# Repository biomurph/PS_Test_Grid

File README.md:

# PS_Test_Grid
Test grid for PS Hardware Revision

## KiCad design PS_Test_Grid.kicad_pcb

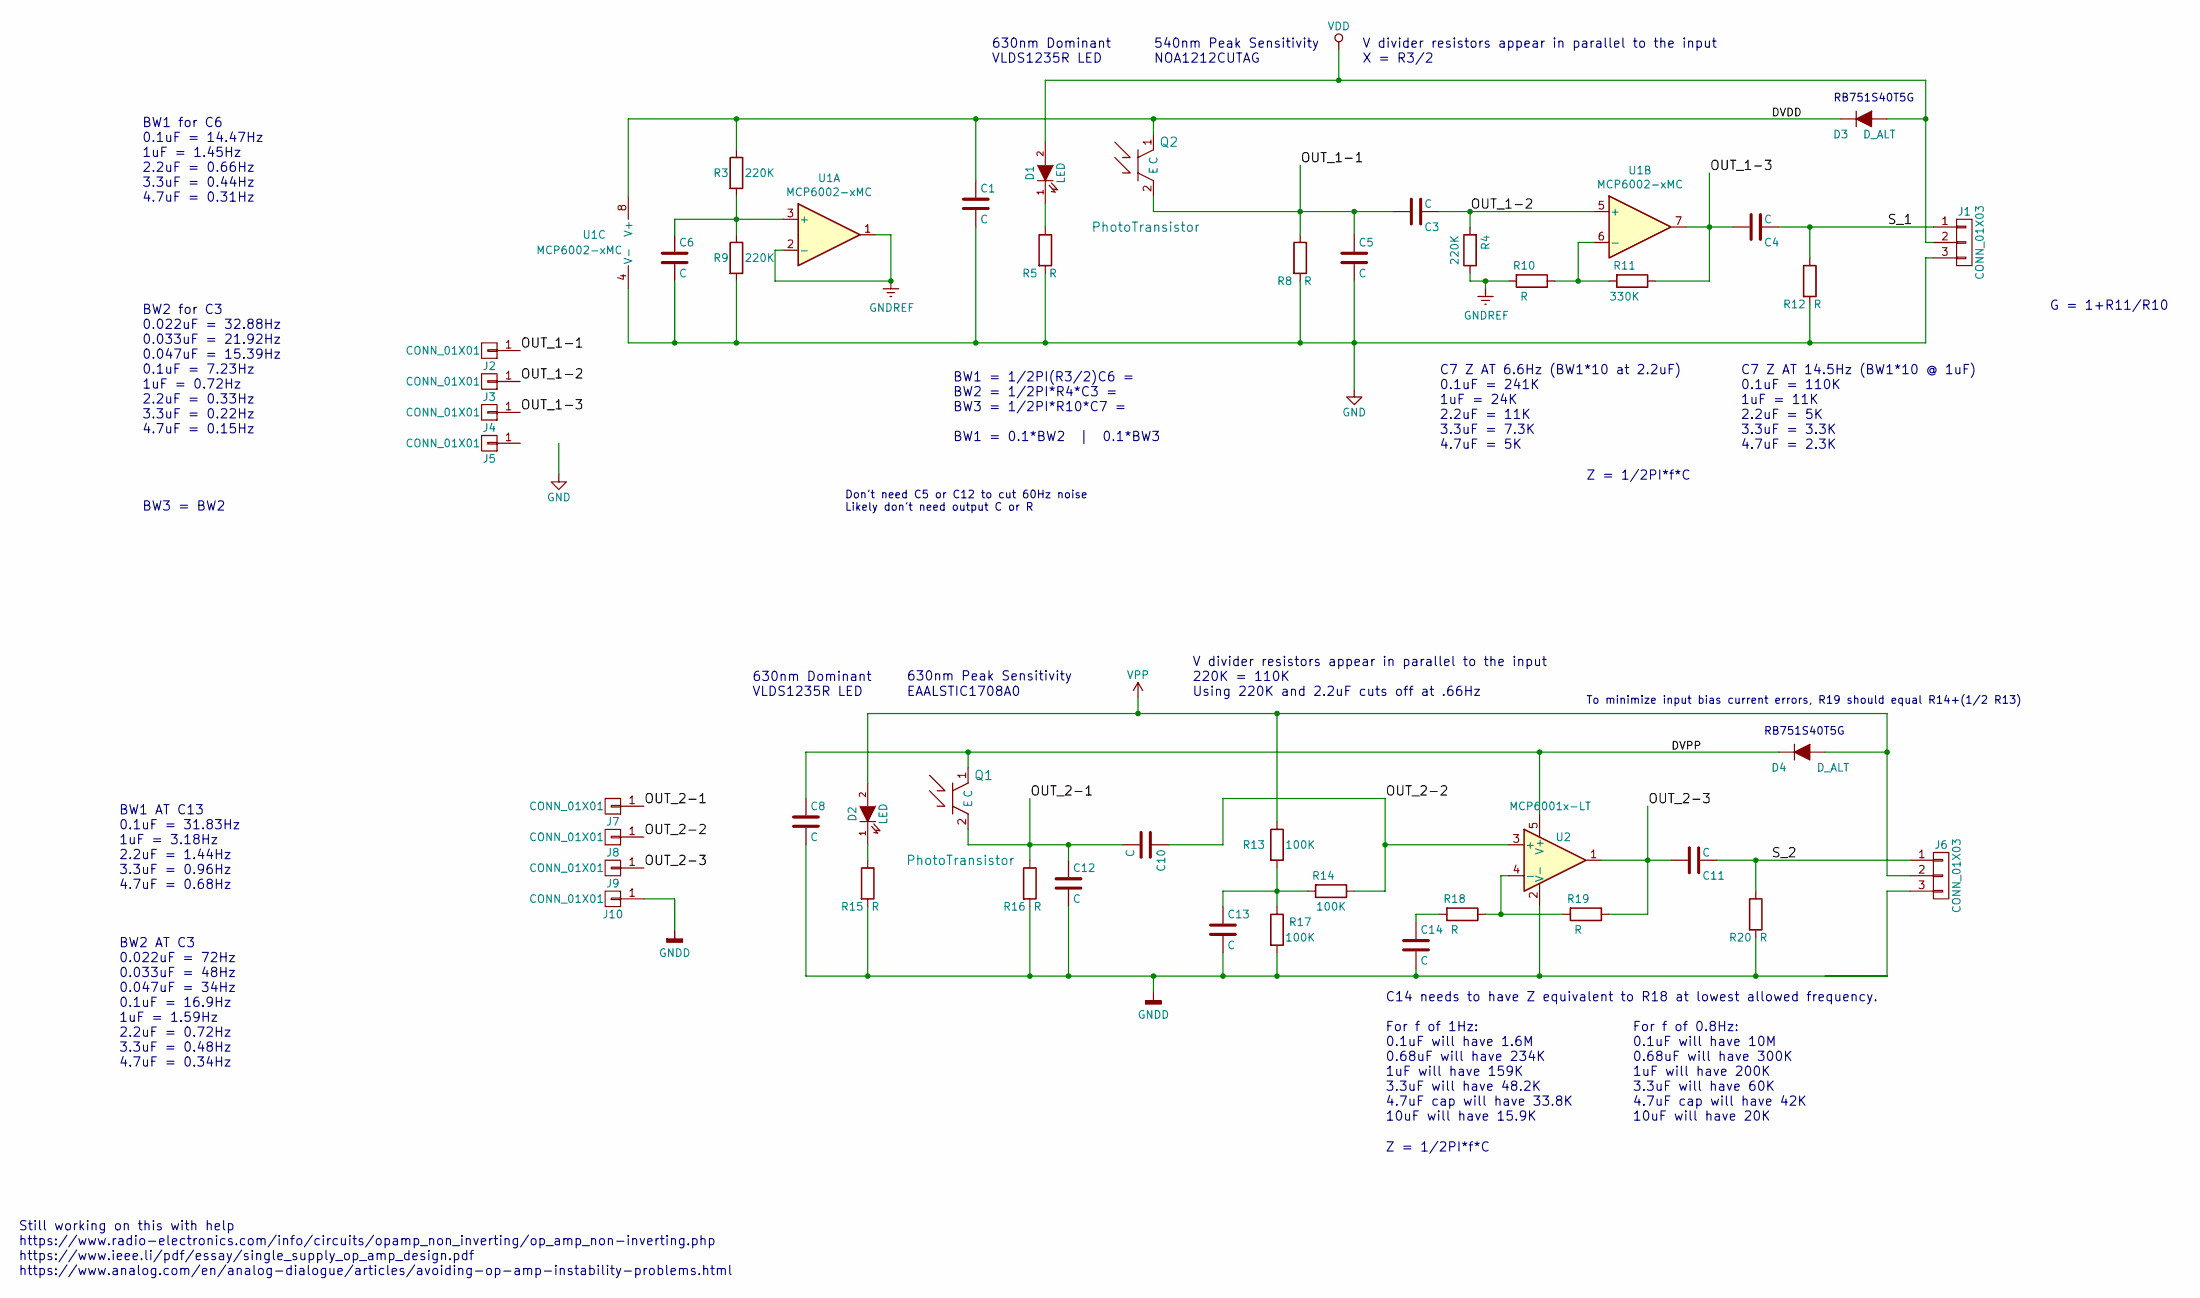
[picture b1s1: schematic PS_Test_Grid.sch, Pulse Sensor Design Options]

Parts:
C1, C3, C4, C5, C6, C8, C10, C11, C12, C13, C14: C; C_0603
D1, D2: LED; VLD1235R_LED
D3, D4: D_ALT; RB751S40T5G_DIODE
J1, J6: CONN_01X03; Pin_Header_Straight_1x03_Pitch2.54mm
J2, J3, J4, J5, J7, J8, J9, J10: CONN_01X01; Pin_Header_Straight_1x01_Pitch1.00mm
Q1, Q2: PhotoTransistor; EAALSTIC1708A0
R3, R4, R9: 220K; C_0603
R5, R8, R10, R12, R15, R16, R18, R19, R20: R; C_0603
R11: 330K; C_0603
R13, R14, R17: 100K; C_0603
U1: MCP6002-xMC; DFN-8-1EP_3x2mm_P0.5mm_EP1.75x1.45mm
U2: MCP6001x-LT; SOT-353_SC-70-5

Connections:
/DVDD: C1.1, D3.1 (K), Q2.1 (C), R3.1, U1.8 (V+)
/DVPP: C8.1, D4.1 (K), Q1.1 (C), U2.5 (V+)
/OUT_1-1: C3.2, C5.1, J2.1, Q2.2 (E), R8.1
/OUT_1-2: C3.1, J3.1, R4.2, U1.5 (+)
/OUT_1-3: C4.2, J4.1, R11.1, U1.7
/OUT_2-1: C10.2, C12.1, J7.1, Q1.2 (E), R16.1
/OUT_2-2: C10.1, J8.1, R14.1, U2.3 (+)
/OUT_2-3: C11.2, J9.1, R19.1, U2.1
/S_1: C4.1, J1.1, R12.1
/S_2: C11.1, J6.1, R20.1
GND: C1.2, C5.2, C6.2, J1.3, J5.1, R5.2, R8.2, R9.2, R12.2, U1.4 (V-), U1.9 (V-)
GNDD: C8.2, C12.2, C13.2, C14.2, J6.3, J10.1, R15.2, R16.2, R17.2, R20.2, U2.2 (V-)
GNDREF: R4.1, R10.2, U1.1, U1.2 (-)
unnamed: C6.1, R3.2, R9.1, U1.3 (+)
unnamed: C13.1, R13.2, R14.2, R17.1
unnamed: C14.1, R18.2
unnamed: D1.1 (K), R5.1
unnamed: D2.1 (K), R15.1
unnamed: R10.1, R11.2, U1.6 (-)
unnamed: R18.1, R19.2, U2.4 (-)
VDD: D1.2 (A), D3.2 (A), J1.2
VPP: D2.2 (A), D4.2 (A), J6.2, R13.1

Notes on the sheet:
EAALSTIC1708A0
V divider resistors appear in parallel to the input X = R3/2
Still working on this with help https://www.radio-electronics.com/info/circuits/opamp_non_inverting/op_amp_non-inverting.php https://www.ieee.li/pdf/essay/single_supply_op_amp_design.pdf https://www.analog.com/en/analog-dialogue/articles/avoiding-op-amp-instability-problems.html
V divider resistors appear in parallel to the input 220K = 110K Using 220K and 2.2uF cuts off at .66Hz
C14 needs to have Z equivalent to R18 at lowest allowed frequency. For f of 1Hz: 0.1uF will have 1.6M 0.68uF will have 234K 1uF will have 159K 3.3uF will have 48.2K 4.7uF cap will have 33.8K 10uF will have 15.9K
630nm Peak Sensitivity
630nm Dominant VLDS1235R LED
540nm Peak Sensitivity NOA1212CUTAG
For f of 0.8Hz: 0.1uF will have 10M 0.68uF will have 300K 1uF will have 200K 3.3uF will have 60K 4.7uF cap will have 42K 10uF will have 20K
Z = 1/2PI*f*C
BW1 = 1/2PI(R3/2)C6 = BW2 = 1/2PI*R4*C3 = BW3 = 1/2PI*R10*C7 = BW1 = 0.1*BW2 | 0.1*BW3
BW1 for C6 0.1uF = 14.47Hz 1uF = 1.45Hz 2.2uF = 0.66Hz 3.3uF = 0.44Hz 4.7uF = 0.31Hz
BW1 AT C13 0.1uF = 31.83Hz 1uF = 3.18Hz 2.2uF = 1.44Hz 3.3uF = 0.96Hz 4.7uF = 0.68Hz
BW2 for C3 0.022uF = 32.88Hz 0.033uF = 21.92Hz 0.047uF = 15.39Hz 0.1uF = 7.23Hz 1uF = 0.72Hz 2.2uF = 0.33Hz 3.3uF = 0.22Hz 4.7uF = 0.15Hz
BW3 = BW2
C7 Z AT 6.6Hz (BW1*10 at 2.2uF) 0.1uF = 241K 1uF = 24K 2.2uF = 11K 3.3uF = 7.3K 4.7uF = 5K
BW2 AT C3 0.022uF = 72Hz 0.033uF = 48Hz 0.047uF = 34Hz 0.1uF = 16.9Hz 1uF = 1.59Hz 2.2uF = 0.72Hz 3.3uF = 0.48Hz 4.7uF = 0.34Hz
C7 Z AT 14.5Hz (BW1*10 @ 1uF) 0.1uF = 110K 1uF = 11K 2.2uF = 5K 3.3uF = 3.3K 4.7uF = 2.3K
G = 1+R11/R10
RB751S40T5G
To minimize input bias current errors, R19 should equal R14+(1/2 R13)
Don’t need C5 or C12 to cut 60Hz noise Likely don’t need output C or R

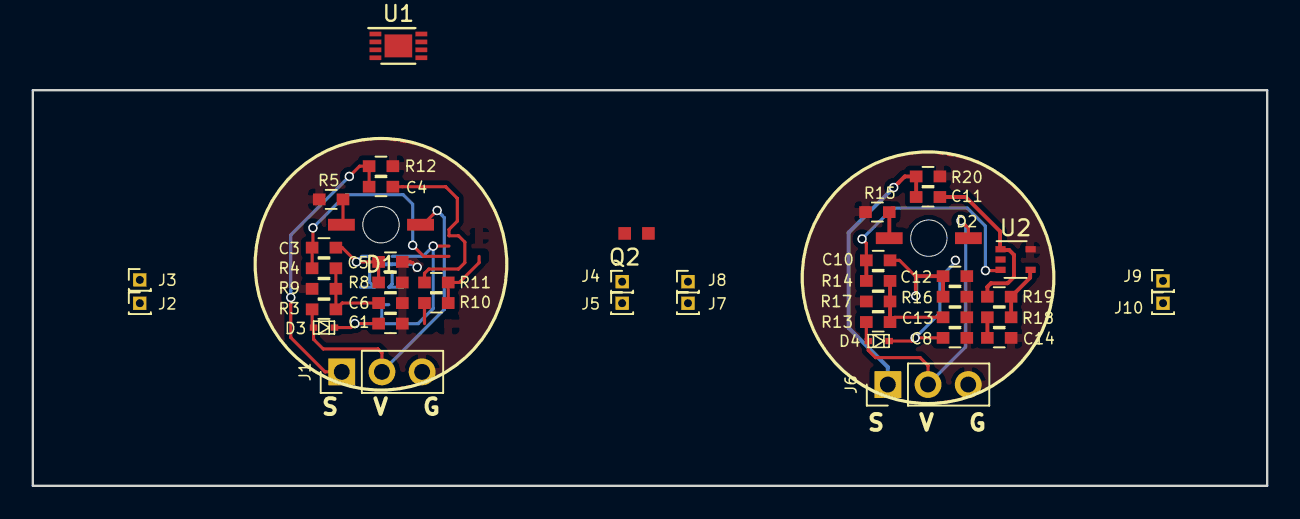
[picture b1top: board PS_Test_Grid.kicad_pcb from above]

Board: 2 copper layers, 78.0 x 25.0 mm, 45 parts (1 on the bottom side), 22 nets.

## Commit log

2018-08-28 SETTING UP
2018-09-01 Laid out HPF candidate
2018-09-02 Working out the filter and amplification designs to trial
2018-09-11 laid out the footprints
2018-11-19 moved test points and cleaned schematic
2018-11-20 working out component value scheme
2018-11-26 saved notes
2018-11-27 upgraded to KiCad 5
2018-11-28 Layout Circuit Add Protection Diode to Schem
2018-11-30 laid out all drc pass
2018-11-30 adjusted protection diode. Reroute
2019-10-07 added dual op amp circuit
    ready to be laid out
2021-04-28 minor notes
